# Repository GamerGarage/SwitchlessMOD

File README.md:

# Sega Mega Drive - PIC16F684 Switchless Region & Reset Mod

Este proyecto contiene el firmware en C para un microcontrolador PIC16F684 diseñado específicamente para realizar un mod "switchless" (sin interruptores físicos) en la **Sega Mega Drive** (o Genesis). 

Permite controlar el reinicio y cambiar la región (PAL/JAP/USA) de la consola utilizando únicamente el botón de RESET original. Además, utiliza un LED RGB para indicar visualmente en qué región se encuentra el sistema en cada momento.

## 🚀 Características

* **Control con un solo botón:** Discrimina entre pulsaciones cortas (reinicio) y pulsaciones largas (cambio de región) interceptando el botón de RESET original de la Mega Drive.
* **Memoria EEPROM:** Guarda la última región seleccionada para que la consola arranque con ella la próxima vez que se encienda.
* **Indicador LED RGB:** Muestra visualmente la región actual (Rojo = PAL, Verde = JAP, Azul = USA). Sustituye al LED rojo original de la consola.
* **Antirrebote por software:** Evita falsas pulsaciones y reinicios accidentales.

## 🧩 Circuito Impreso (PCB) Personalizado y Gerbers

Para facilitar la instalación y hacerla lo más limpia posible, he diseñado una placa de circuito impreso (PCB) a medida para este mod.

### Vista de la PCB

### Esquemático (KiCad)

* **Descarga de Gerbers:** Puedes descargar los archivos **Gerber** incluidos en este repositorio para pedir tus placas en JLCPCB, PCBWay, etc.
* **Resistencias LED RGB:** Deben ir soldadas exactamente en las posiciones marcadas como **R1, R2 y R3** en la serigrafía.
* **Uso Multipropósito (Breakout Board):** El diseño de la placa es genérico. Si puenteas con estaño las posiciones de las resistencias R1, R2 y R3, puedes usar esta PCB como un adaptador genérico para cualquier otro proyecto con el PIC16F684.
* **Puerto de Programación (ICSP):** La placa incluye pines para programar el PIC directamente sobre la PCB con un PICkit 3.

## ⚙️ Funcionamiento de la Intercepción del Reset

El PIC actúa como un "intermediario" entre el botón físico de la consola y el procesador. 

1.  **Pulsación Corta (menos de 2 segundos):** El PIC detecta la pulsación y transmite una señal de reinicio (LOW) al procesador durante 200ms. Funciona como un reset tradicional.
2.  **Pulsación Larga (más de 2 segundos):** El PIC **NO** envía la señal de reinicio a la consola. En su lugar, entra en el "Modo de Selección" de región. 
    * El LED RGB ciclará entre los tres colores cada 500ms.
    * Al soltar el botón en el color deseado, la selección se guarda en la EEPROM y cambia la región al instante, sin reiniciar el juego.

### Zonas y Colores
| Región | Video | Idioma | Color LED RGB |
| :--- | :--- | :--- | :--- |
| **PAL (Europa)** | 50Hz (0) | Inglés (1) | 🔴 Rojo |
| **JAP (Japón)** | 60Hz (1) | Japonés (0) | 🟢 Verde |
| **USA (América)**| 60Hz (1) | Inglés (1) | 🔵 Azul |

## 🔌 Conexiones de la PCB al Hardware

La serigrafía de mi PCB está diseñada para ser intuitiva. Aquí tienes la correspondencia de los pads con los puntos de soldadura en la consola:

| Pad en la PCB | Pin PIC | Función / Conexión en la Mega Drive |
| :--- | :---: | :--- |
| **RESET IN** | `RA4` | Al botón físico de Reset (la parte que va a GND al pulsar). |
| **RESET OUT** | `RA5` | Al punto de la pista de Reset que va hacia el procesador principal. |
| **LANG** | `RC0` | Al punto del jumper de configuración de Idioma. |
| **50/60hz** | `RA2` | Al punto del jumper de configuración de Frecuencia. |
| **RC3/R** | `RC3` | Al ánodo Rojo del LED RGB (vía resistencia R1). |
| **RC4/G** | `RC4` | Al ánodo Verde del LED RGB (vía resistencia R2). |
| **RC5/B** | `RC5` | Al ánodo Azul del LED RGB (vía resistencia R3). |
| **VCC** | `VDD` | Alimentación de +5V de la consola. |
| **GND** | `VSS` | Tierra (GND) de la consola. |

*Nota: El cátodo común del LED RGB se conecta a cualquiera de los pads **GND** extra disponibles en la PCB.*

## ✂️ Guía de Instalación: Ejemplo Placa IC BD M5 PAL / VA6

⚠️ **IMPORTANTE:** Es **ESTRICTAMENTE NECESARIO** cortar pistas en la placa base original. Si conectas el PIC sin aislar los pines, provocarás un cortocircuito que podria dañará la consola o el microcontrolador.

Para ilustrar el proceso, aquí tienes mi propia instalación en una revisión **VA6**:

### 1. Intercepción del botón RESET
Debes localizar la pista que une el botón de Reset con el procesador y **cortarla**. 
* El lado de la pista que viene del botón físico se suelda al pad **RESET IN** de la PCB.
* El lado de la pista que va hacia el procesador se suelda al pad **RESET OUT** de la PCB.

### 2. Configuración de Región (Jumpers)
En la revisión VA6, el idioma y la frecuencia vienen fijados por los jumpers **JP2** y **JP3**. 
* **Cortar pistas:** Corta la pista de cobre que une los pads de estos jumpers para romper la conexión de fábrica (+5V y GND). Comprueba con un multímetro que están aislados.
* **Conexión de señales:** Suelda los pads **LANG** y **50/60hz** del mod a los puntos correspondientes de los jumpers que van hacia el chip de video.
* **Alimentación:** Puedes aprovechar el otro extremo de los jumpers cortados para alimentar el mod. El lado cortado de JP2 te dará los +5V (suelda a **VCC**) y el lado cortado de JP3 te dará la masa (suelda a **GND**).

## 🛠️ Compilación y Programación

* **IDE:** MPLAB X IDE
* **Compilador:** XC8 Compiler
* **Frecuencia del Oscilador:** 4MHz (Oscilador Interno)

Utiliza un programador como el **PICkit 3** conectándolo a los pines ICSP de la PCB para flashear el archivo `.hex`.

## ⚠️ Advertencia Legal y de Hardware
Modificar hardware original conlleva riesgos. Asegúrate de tener conocimientos de electrónica y revisar bien los puntos de corte de tu revisión específica de placa base (VA0, VA4, VA6, etc.) antes de proceder. El software y los esquemas se proporcionan "tal cual". No me hago responsable por daños ocasionados a tu equipo.

---

## 👨‍💻 Autor y Contacto

Creado por **Javi** de **GAMER GARAGE**. 

Si te ha resultado útil este mod o quieres ver más proyectos de reparación, modificación y electrónica retro, pásate por mi web:
🌐 **[www.gamergarage.es](https://www.gamergarage.es)**

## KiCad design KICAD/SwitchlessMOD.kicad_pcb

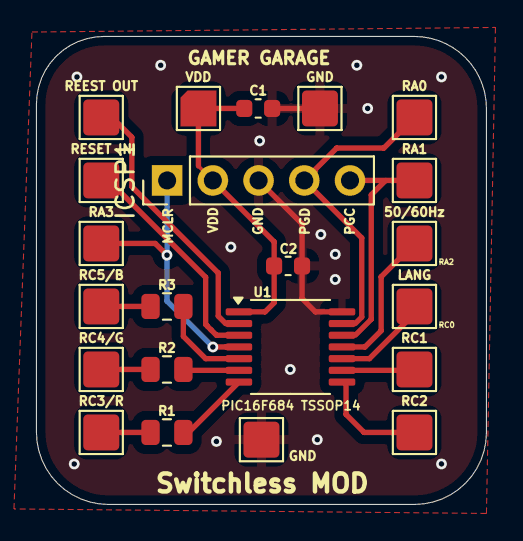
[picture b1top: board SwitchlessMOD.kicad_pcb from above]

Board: 2 copper layers, 25.0 x 26.0 mm, 22 parts (0 on the bottom side), 17 nets.

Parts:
50/60Hz: TestPoint_Pad_2.0x2.0mm
C1, C2: C; C_0603_1608Metric
GND: TestPoint_Pad_2.0x2.0mm
GND#2: TestPoint_Pad_2.0x2.0mm
ICSP1: Conn_01x05_Pin; PinHeader_1x05_P2.54mm_Vertical
LANG: TestPoint_Pad_2.0x2.0mm
R1, R2, R3: R; R_0805_2012Metric
RA0, RA1, RA3: TestPoint_Pad_2.0x2.0mm
RC1, RC2, RC3/R, RC4/G, RC5/B: TestPoint_Pad_2.0x2.0mm
REEST OUT: TestPoint_Pad_2.0x2.0mm
RESET IN: TestPoint_Pad_2.0x2.0mm
U1: PIC16F684-IP; TSSOP-14_4.4x5mm_P0.65mm
VDD: TestPoint_Pad_2.0x2.0mm

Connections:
B: R3.2, RC5/B.5
G: R2.2, RC4/G.6
LANG: LANG.10, U1.10 (C2IN+/AN4/RC0)
unnamed: R3.1, U1.5 (P1A/CCP1/RC5)
unnamed: R2.1, U1.6 (P1B/C2OUT/RC4)
unnamed: R1.1, U1.7 (P1C/AN7/RC3)
R: R1.2, RC3/R.7
RA0: ICSP1.4, RA0.13, U1.13 (RA0/AN0/C1IN+/ICSPDAT/ULPWU)
RA1: ICSP1.5, RA1.12, U1.12 (RA1/AN1/C1IN-/Vref/ICSPCLK)
RA3: ICSP1.1, RA3.4, U1.4 (RA3/~MCLR/Vpp)
RC1: RC1.9, U1.9 (C2IN-/AN5/RC1)
RC2: RC2.8, U1.8 (P1D/AN6/RC2)
RESET IN: RESET IN.3, U1.3 (RA4/AN3/~T1G/OSC2/CLKOUT)
RESET OUT: REEST OUT.2, U1.2 (RA5/T1CKI/OSC1/CLKIN)
VDD: C1.1, C2.1, ICSP1.2, U1.1 (VDD), VDD.1
VIDEO 50/60HZ: 50/60Hz.11, U1.11 (RA2/AN2/T0CKI/INT/C1OUT)
VSS: C1.2, C2.2, GND.14, GND#2.14, ICSP1.3, U1.14 (VSS)

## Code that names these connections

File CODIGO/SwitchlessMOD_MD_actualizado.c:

/*
 * ----------------------------------------------------------------------------
 * Sega Mega Drive - PIC16F684 Switchless Region & Reset Mod
 * ----------------------------------------------------------------------------
 * Autor:   Javi (GAMER GARAGE)
 * Web:     https://www.gamergarage.es
 * Versión: 1.0
 * * Descripción: 
 * Firmware para controlar el reinicio y la región (PAL/JAP/USA) de una 
 * consola Sega Mega Drive/Genesis utilizando el botón de RESET original
 * y un indicador LED RGB.
 * * Licencia: MIT (Puedes usar, modificar y distribuir este código libremente, 
 * siempre y cuando se mantenga la mención al autor original).
 * ----------------------------------------------------------------------------
 */

// PIC16F684 Configuration Bit Settings
#pragma config FOSC = INTOSCIO  // Oscilador interno activado
// ... (aquí sigue tu código normal)

// PIC16F684 Configuration Bit Settings
#pragma config FOSC = INTOSCIO  // Oscilador interno activado
#pragma config WDTE = OFF       // Watchdog Timer desactivado
#pragma config PWRTE = OFF      // Power-up Timer desactivado
#pragma config MCLRE = OFF      // Pin MCLR configurado como pin de I/O digital
#pragma config CP = OFF         // Protección de código desactivada
#pragma config CPD = OFF        // Protección de datos desactivada
#pragma config BOREN = OFF      // Brown-out Reset desactivado
#pragma config IESO = ON        // Internal External Switchover activado
#pragma config FCMEN = ON       // Fail-Safe Clock Monitor activado

#include <xc.h>
#include <stdio.h>
#include <pic16f684.h>

// Definición de la frecuencia del oscilador para el uso de la función __delay_ms()
#define _XTAL_FREQ 4000000

// Asignación de pines para el LED RGB indicador de región
#define LED_RED    RC3
#define LED_GREEN  RC4
#define LED_BLUE   RC5

// Asignación de pines para el control de Reset
#define RESET_IN   RA4  // Botón de entrada para el reset y cambio de región
#define RESET_OUT  RA5  // Salida que ejecuta el reset físico en la consola

// Asignación de pines para la configuración de región (Idioma y Video)
#define LANGUAGE   RC0
#define VIDEO      RA2

// Constantes arbitrarias para identificar cada región en la EEPROM
#define PAL        0x50
#define JAP        0x4A
#define USA        0x55

/**
 * Guarda el modo de región actual en la memoria EEPROM.
 */
void saveMode(unsigned char dir, unsigned char data) {
    eeprom_write(dir, data);
}

/**
 * Configura las salidas y el LED para el modo PAL (Europa).
 */
void setPAL(void){
    LANGUAGE = 1;
    VIDEO = 0;
    LED_RED = 1;
    LED_GREEN = 0;
    LED_BLUE = 0;
}

/**
 * Configura las salidas y el LED para el modo JAP (Japón).
 */
void setJAP(void){
    LANGUAGE = 0;
    VIDEO = 1;
    LED_RED = 0;
    LED_GREEN = 1;
    LED_BLUE = 0;
}

/**
 * Configura las salidas y el LED para el modo USA (Estados Unidos).
 */
void setUSA(void){
    LANGUAGE = 1;
    VIDEO = 1;
    LED_RED = 0;
    LED_GREEN = 0;
    LED_BLUE = 1;
}

/**
 * Lee la memoria EEPROM y aplica la configuración de región guardada.
 * Si no reconoce el dato (ej. primera vez que se enciende), carga PAL por defecto.
 */
void loadMode(unsigned char dir) {
    unsigned char storedMode = eeprom_read(dir);
    
    switch (storedMode){
        case PAL:
            setPAL();
            break;
        case JAP:
            setJAP();
            break;
        case USA:
            setUSA();
            break;
        default:
            setPAL();          
    }
}

/**
 * Bucle de selección de región.
 * Cambia cíclicamente entre PAL, JAP y USA cada 500ms mientras el botón
 * se mantenga pulsado. Al soltarlo, guarda la selección final en la EEPROM.
 */
void changeMode(void){
    unsigned char selectedMode;
    // Mientras el botón esté presionado (!RESET_IN por el pull-up)
    while (!RESET_IN){
        setPAL(); 
        selectedMode = PAL;
        __delay_ms (500);
        if (RESET_IN) break; // Si se suelta el botón, salimos del bucle

        setJAP();    
        selectedMode = JAP;
        __delay_ms (500);
        if (RESET_IN) break;

        setUSA();  
        selectedMode = USA;
        __delay_ms (500);
        if (RESET_IN) break;
    }
    // Guardar el modo seleccionado en la dirección 0x00 de la EEPROM
    saveMode(0x00, selectedMode);
}

void main(void) {
    // Configuración inicial del microcontrolador
    ANSEL = 0;               // Desactiva todas las entradas analógicas (todo digital)
    TRISA = 0b00010000;      // Puerto A: RA4 como entrada (Botón), resto como salidas
    TRISC = 0b00000000;      // Puerto C: Todos los pines como salidas

    // Configuración de la resistencia Pull-up interna para el botón
    OPTION_REGbits.nRAPU = 0;  // Habilita el control global de los pull-ups en el Puerto A
    WPUA |= (1 << 4);          // Activa el pull-up específico en el pin RA4

    // Estado inicial seguro
    RESET_OUT = 1;           // Mantiene la señal de reset de la consola en estado inactivo

    // Cargar la última configuración de región guardada
    loadMode(0x00);

    int tiempo_pulsado = 0;

    // Bucle principal del programa
    while (1) {
        RESET_OUT = 1;              // Asegura que el RESET esté desactivado    
        int tiempo_pulsado = 0;     // Reinicia el contador de tiempo de pulsación

        // Bucle de espera activa: cuenta los milisegundos mientras el botón está pulsado
        while (!RESET_IN) {
            __delay_ms(1);
            tiempo_pulsado++;

            // Condición de Pulsación Larga: Modo de cambio de región (> 2 segundos)
            if (tiempo_pulsado >= 2000) {
                changeMode();

                // Esperar a que el usuario suelte el botón por completo antes de continuar
                while (!RESET_IN);     // Bucle infinito hasta que RESET_IN vuelva a ser 1
                __delay_ms(50);        // Pequeño retardo antirrebote
                break;                 // Salir de este bucle para volver al principal
            }
        }

        // Condición de Pulsación Corta: Ejecutar Reset de la consola (entre 20ms y 2s)
        if (tiempo_pulsado > 20 && tiempo_pulsado < 2000) {
            RESET_OUT = 0;            // Activar señal de reset (Lógica negativa)        
            __delay_ms(200);          // Mantener el reset presionado artificialmente por 200ms
            RESET_OUT = 1;            // Liberar el reset
        }

        // Pequeña espera antirrebote general al terminar cualquier acción
        __delay_ms(50);
    }
    
    return;

}

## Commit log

2026-02-19 Update README.md
    primera actualizacion del readme
2026-02-19 Archivos del proyecto
    Se añaden los archivos de KiCAD, los gerber y el codigo fuente.
2026-02-19 Update README.md
    actaulizacion con imagenes pcb
2026-02-19 Add files via upload
    imagene pcb
2026-02-19 Create LICENSE
